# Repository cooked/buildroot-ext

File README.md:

# Buildroot Ext(ensions)

This repository contains custom Buildroot configurations for:

- Raspberry Pi 3B+, with real-time kernel (PREEMPT_RT patch)
- Raspberry Pi 4, with real-time kernel (PREEMPT_RT patch)

## How to use it

This repository is an add-on to Buildroot and it is meant to be configured as an external Buildroot folder defining the BR2_EXTERNAL variable, as described in the [official manual](https://buildroot.org/downloads/manual/manual.html#outside-br-custom)

```bash

git clone https://github.com/cooked/buildroot-ext.git

# get buildroot (skip if you have it already)
git clone https://github.com/buildroot/buildroot.git

cd buildroot

# use an explicit Buildroot release (optional)
git fetch --all --tags
git checkout <release_tag> -b <release_tag>

# configure the external folder (do nothing, exit without saving)
make BR2_EXTERNAL=../buildroot-ext menuconfig

# check new custom configs are listed
make list-defconfigs

# load config and build
make raspberrypi3_rt_defconfig
make
```

## Reference

Read more about [Buildroot basics](https://www.stefanocottafavi.com/buildroot_basics/) and how to [build a realtime Linux kernel](https://www.stefanocottafavi.com/buildroot_rpi_kernel_rt/) with it.

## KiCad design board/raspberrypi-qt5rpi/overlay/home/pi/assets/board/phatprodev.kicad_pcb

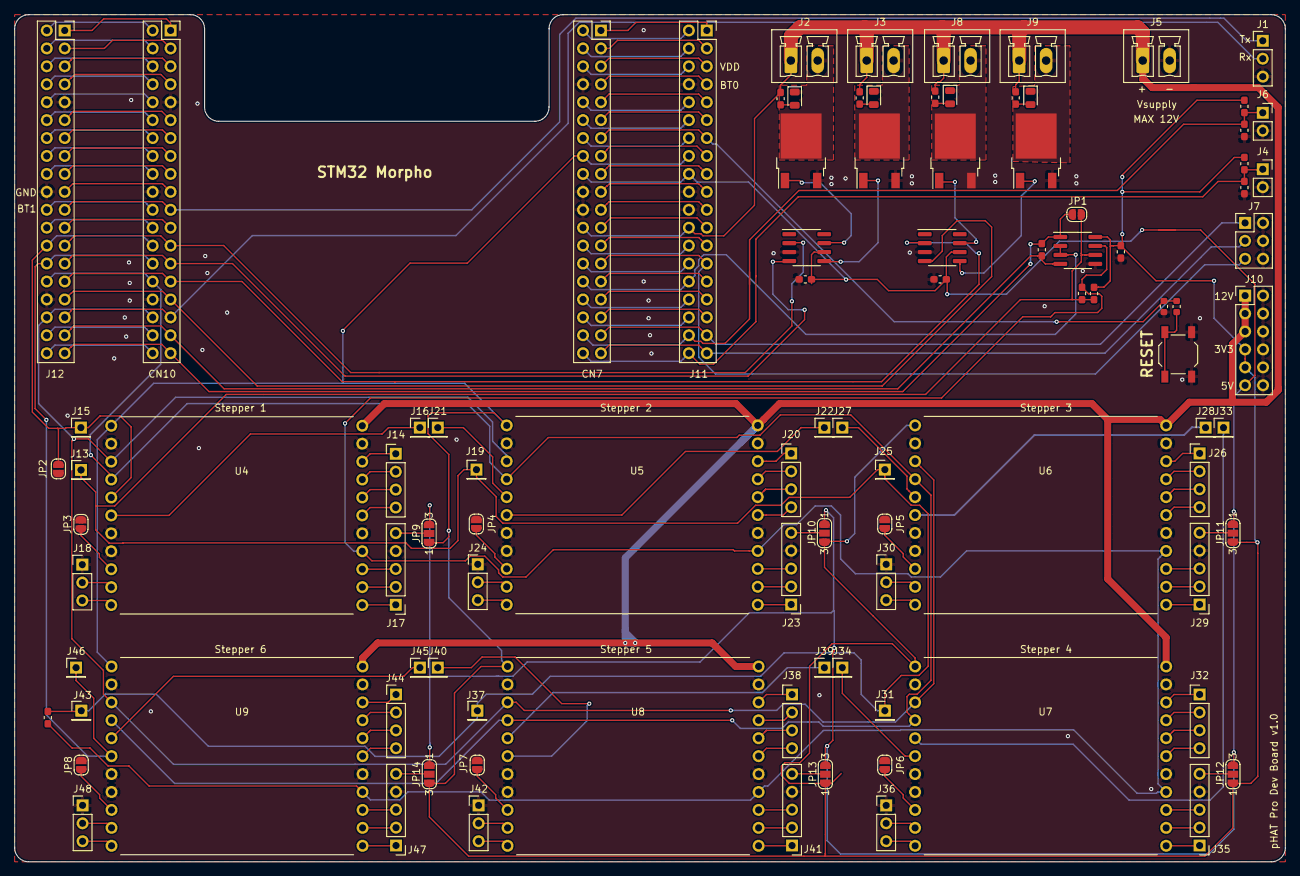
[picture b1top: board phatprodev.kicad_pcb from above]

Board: 2 copper layers, 180.0 x 120.0 mm, 99 parts (0 on the bottom side), 162 nets.

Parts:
C1, C2, C3, C4, C5: 100n; C_0603_1608Metric_Pad1.05x0.95mm_HandSolder
C6: 100n; C_0603_1608Metric
CN7, CN10: Conn_02x19_Odd_Even; PinSocket_2x19_P2.54mm_Vertical
D1, D2, D3, D4: LED; LED_0805_2012Metric
J1, J18, J24, J30, J36, J42, J48: Conn_01x03; PinHeader_1x03_P2.54mm_Vertical
J2, J3, J5, J8, J9: Conn_01x02; PhoenixContact_MCV_1,5_2-G-3.81_1x02_P3.81mm_Vertical
J4, J6: Conn_01x02; PinSocket_1x02_P2.54mm_Vertical
J7: Conn_02x03_Odd_Even; PinHeader_2x03_P2.54mm_Vertical
J10: Conn_02x06_Odd_Even; PinHeader_2x06_P2.54mm_Vertical
J11, J12: Conn_02x19_Odd_Even; PinSocket_2x19_P2.54mm_Vertical
J13, J15, J16, J19, J21, J22, J25, J27, J28, J31, J33, J34, J37, J39, J40, J43, J45, J46: Conn_01x01; PinHeader_1x01_P2.54mm_Vertical
J14, J20, J26, J32, J38, J44: Conn_01x04; PinHeader_1x04_P2.54mm_Vertical
J17, J23, J29, J35, J41, J47: Conn_01x05; PinHeader_1x05_P2.54mm_Vertical
JP1, JP2, JP3, JP4, JP5, JP6, JP7, JP8: SolderJumper_2_Open; SolderJumper-2_P1.3mm_Open_RoundedPad1.0x1.5mm
JP9, JP10, JP11, JP12, JP13, JP14: Jumper_3_Open; SolderJumper-3_P1.3mm_Open_RoundedPad1.0x1.5mm_NumberLabels
Q1, Q2, Q3, Q4: IRLR3636TRPBF; TO-252-2
R1, R5: 10k; R_0603_1608Metric_Pad1.05x0.95mm_HandSolder
R2, R6: 1k; R_0603_1608Metric_Pad1.05x0.95mm_HandSolder
R3, R4, R8, R9: 3k3; R_0603_1608Metric_Pad1.05x0.95mm_HandSolder
R7, R10: 120; R_0603_1608Metric_Pad1.05x0.95mm_HandSolder
R11: 10k; R_0603_1608Metric
SW1: SW_DIP_x01; SW_SPST_TL3342
U1, U2: UCC27524; SOIC-8_3.9x4.9mm_P1.27mm
U3: ST1480ACDR; SOIC-8_3.9x4.9mm_P1.27mm
U4, U5, U6, U7, U8, U9: TMC5160_BOB

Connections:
+3V3: C3.2, CN7.16, J10.7, J10.9, J11.16, JP9.1, JP10.1, JP11.1, JP12.1, JP13.1, JP14.1, R1.1, R2.1, R5.1, U3.8, U4.1, U5.1, U6.1, U7.1, U8.1, U9.1
+5V: C1.1, C4.1, CN7.18, J10.11, J11.18, JP9.3, JP10.3, JP11.3, JP12.3, JP13.3, JP14.3, U1.6, U2.6
+12V: CN7.24, J2.1, J3.1, J5.1, J8.1, J9.1, J10.1, J10.3, J10.5, J11.24, R3.2, R4.2, R8.2, R9.2, U4.12, U5.12, U6.12, U7.12, U8.12, U9.12
/BOOT0: CN7.7, J11.7
/BOOT1: CN10.22, J12.22
/CN7_1: CN7.1, J11.1
/CN7_2: CN7.2, J11.2
/CN7_3: CN7.3, J11.3
/CN7_4: CN7.4, J11.4
/CN7_5: CN7.5, J11.5
/CN7_6: CN7.6, J11.6
/CN7_9: CN7.9, J11.9
/CN7_10: CN7.10, J11.10
/CN7_11: CN7.11, J11.11
/CN7_12: CN7.12, J11.12
/CN7_14: CN7.14, J11.14
/CN7_15: CN7.15, J11.15
/CN7_17: CN7.17, J11.17
/CN7_19: CN7.19, J11.19
/CN7_21: CN7.21, J11.21
/CN7_23: CN7.23, J11.23
/CN7_25: CN7.25, J11.25
/CN7_26: CN7.26, J11.26
/CN7_27: CN7.27, J7.5, J11.27
/CN7_28: CN7.28, J11.28
/CN7_29: CN7.29, J11.29
/CN7_31: CN7.31, J11.31
/CN7_32: CN7.32, J11.32
/CN7_33: CN7.33, J11.33
/CN7_34: CN7.34, J11.34
/CN7_35: CN7.35, J7.1, J11.35
/CN7_37: CN7.37, J7.3, J11.37
/CN10_1: CN10.1, J12.1
/CN10_2: CN10.2, J12.2
/CN10_3: CN10.3, J12.3
/CN10_4: CN10.4, J12.4
/CN10_5: CN10.5, J12.5
/CN10_6: CN10.6, J12.6
/CN10_7: CN10.7, J12.7
/CN10_8: CN10.8, J12.8
/CN10_10: CN10.10, J12.10
/CN10_11: CN10.11, J12.11
/CN10_12: CN10.12, J12.12
/CN10_13: CN10.13, J12.13
/CN10_14: CN10.14, J12.14
/CN10_15: CN10.15, J12.15
/CN10_16: CN10.16, J12.16
/CN10_17: CN10.17, J12.17
/CN10_18: CN10.18, J12.18
/CN10_19: CN10.19, J12.19
/CN10_23: CN10.23, J12.23
/CN10_24: CN10.24, J12.24
/CN10_36: CN10.36, J12.36
/CN10_38: CN10.38, J12.38
/CSN: CN10.34, J12.34, U4.3, U5.3, U6.3, U7.3, U8.3, U9.3
/F0: CN10.29, J12.29, U2.2
/F0_M: Q3.1, U2.7
/F1: CN10.31, J12.31, U2.4
/F1_M: Q4.1, U2.5
/H0: CN10.25, J12.25, U1.2
/H0_M: Q1.1, U1.7
/H1: CN10.27, J12.27, U1.4
/H1_M: Q2.1, U1.5
/RESET: C6.1, CN7.13, J11.13, R11.1
/RPI_RX: CN10.33, J1.2, J12.33
/RPI_TX: CN10.21, J1.1, J12.21
/SCK: CN10.30, J12.30, U4.4, U5.4, U6.4, U7.4, U8.4, U9.4
/SDI_uC: CN10.26, J12.26, J15.1, JP2.1, U4.5
/SDO_6: CN10.28, J12.28, J46.1, U9.6
/SWN: R7.1, R10.2, U3.7, U4.19, U5.19, U6.19, U7.19, U8.19, U9.19
/SWP: J13.1, J19.1, J25.1, J31.1, J37.1, J43.1, JP1.1, R2.2, R7.2, R10.1, U3.6
/Stepper 1/DRV_ENN: JP3.1, U4.9
/Stepper 1/NAO-SDO: J16.1, U4.6
/Stepper 2/DRV_ENN: JP4.1, U5.9
/Stepper 2/NAI-SDI: J21.1, U5.5
/Stepper 2/NAO-SDO: J22.1, U5.6
/Stepper 3/DRV_ENN: JP5.1, U6.9
/Stepper 3/NAI-SDI: J27.1, U6.5
/Stepper 3/NAO-SDO: J28.1, U6.6
/Stepper 4/DRV_ENN: JP6.1, U7.9
/Stepper 4/NAI-SDI: J33.1, U7.5
/Stepper 4/NAO-SDO: J34.1, U7.6
/Stepper 5/DRV_ENN: JP7.1, U8.9
/Stepper 5/NAI-SDI: J39.1, U8.5
/Stepper 5/NAO-SDO: J40.1, U8.6
/Stepper 6/DRV_ENN: JP8.1, U9.9
/Stepper 6/NAI-SDI: J45.1, U9.5
/TH0: C2.1, CN7.38, J4.1, J11.38, R1.2
/TH1: C5.1, CN7.36, J6.1, J11.36, R5.2
/TMC_RTS: CN7.30, J11.30, U3.2, U3.3
/TMC_RX: CN10.37, J12.37, JP1.2, R6.1, U3.1
/TMC_TX: CN10.35, J12.35, R6.2, U3.4
GND: C1.2, C2.2, C3.1, C4.2, C5.2, C6.2, CN7.8, CN7.20, CN7.22, CN10.9, CN10.20, CN10.32, J1.3, J4.2, J5.2, J6.2, J7.2, J7.4, J7.6, J10.2, J10.4, J10.6, J10.8, J10.10, J10.12, J11.8, J11.20, J11.22, J12.9, J12.20, J12.32, J17.4, J18.1, J23.4, J24.1, J29.4, J30.1, J35.4, J36.1, J41.4, J42.1, J47.4, J48.1, JP2.2, JP3.2, JP4.2, JP5.2, JP6.2, JP7.2, JP8.2, Q1.3, Q2.3, Q3.3, Q4.3, SW1.2, U1.3, U2.3, U3.5, U4.2, U4.7, U4.8, U4.13, U4.18, U5.2, U5.7, U5.8, U5.13, U5.18, U6.2, U6.7, U6.8, U6.13, U6.18, U7.2, U7.7, U7.8, U7.13, U7.18, U8.2, U8.7, U8.8, U8.13, U8.18, U9.2, U9.7, U9.8, U9.13, U9.18
unnamed: D1.1, J2.2, Q1.2
unnamed: D1.2, R3.1
unnamed: D2.1, J3.2, Q2.2
unnamed: D2.2, R4.1
unnamed: D3.1, J8.2, Q3.2
unnamed: D3.2, R8.1
unnamed: D4.1, J9.2, Q4.2
unnamed: D4.2, R9.1
unnamed: J14.1, U4.14
unnamed: J14.2, U4.15
unnamed: J14.3, U4.16
unnamed: J14.4, U4.17
unnamed: J17.1, U4.22
unnamed: J17.2, U4.21
unnamed: J17.3, U4.20
unnamed: J17.5, JP9.2
unnamed: J18.2, U4.10
unnamed: J18.3, U4.11
unnamed: J20.1, U5.14
unnamed: J20.2, U5.15
unnamed: J20.3, U5.16
unnamed: J20.4, U5.17
unnamed: J23.1, U5.22
unnamed: J23.2, U5.21
unnamed: J23.3, U5.20
unnamed: J23.5, JP10.2
unnamed: J24.2, U5.10
unnamed: J24.3, U5.11
unnamed: J26.1, U6.14
unnamed: J26.2, U6.15
unnamed: J26.3, U6.16
unnamed: J26.4, U6.17
unnamed: J29.1, U6.22
unnamed: J29.2, U6.21
unnamed: J29.3, U6.20
unnamed: J29.5, JP11.2
unnamed: J30.2, U6.10
unnamed: J30.3, U6.11
unnamed: J32.1, U7.14
unnamed: J32.2, U7.15
unnamed: J32.3, U7.16
unnamed: J32.4, U7.17
unnamed: J35.1, U7.22
unnamed: J35.2, U7.21
unnamed: J35.3, U7.20
unnamed: J35.5, JP12.2
unnamed: J36.2, U7.10
unnamed: J36.3, U7.11
unnamed: J38.1, U8.14
unnamed: J38.2, U8.15
unnamed: J38.3, U8.16
unnamed: J38.4, U8.17
unnamed: J41.1, U8.22
unnamed: J41.2, U8.21
unnamed: J41.3, U8.20
unnamed: J41.5, JP13.2
unnamed: J42.2, U8.10
unnamed: J42.3, U8.11
unnamed: J44.1, U9.14
unnamed: J44.2, U9.15
unnamed: J44.3, U9.16
unnamed: J44.4, U9.17
unnamed: J47.1, U9.22
unnamed: J47.2, U9.21
unnamed: J47.3, U9.20
unnamed: J47.5, JP14.2
unnamed: J48.2, U9.10
unnamed: J48.3, U9.11
unnamed: R11.2, SW1.1

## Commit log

2023-12-12 up rpi4 codesys
2023-12-14 codesys v3
2023-12-19 docker
2024-01-06 update cs+dkr cfg
2024-01-07 pi in sudoers, no pwd
2024-01-07 pi BT fw added
2024-03-17 add rpi3 RT
2024-03-24 add qt5rpi
2024-03-26 update qt5rpi
2024-04-16 WIP klipper package
2024-04-18 wip add klipper
2024-04-22 wip klipper
2024-04-25 WIP rpi5
2024-05-01 rename package
2024-05-03 add wrecklab package
2024-05-05 refactor board and config
2024-05-05 wip klipper3d
2024-05-05 klipperz wip
2024-05-07 switch to systemd
2024-05-16 almost there, wip
